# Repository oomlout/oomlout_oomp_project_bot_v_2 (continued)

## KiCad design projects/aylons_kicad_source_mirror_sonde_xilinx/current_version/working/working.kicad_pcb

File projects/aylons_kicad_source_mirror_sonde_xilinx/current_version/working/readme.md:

# kicad_source_mirror
 
## summary 
* id: aylons_kicad_source_mirror_sonde_xilinx
* user: aylons
* name: kicad_source_mirror
* board: sonde_xilinx
* repo: https://github.com/aylons/kicad-source-mirror
* src_file_repo_kicad_pcb: demos/sonde xilinx/sonde xilinx.kicad_pcb
* src_file_repo_kicad_pcb_link: https://github.com/aylons/kicad-source-mirror/tree/master/demos/sonde xilinx/sonde xilinx.kicad_pcb

* src_file_repo_sch: demos/sonde xilinx/sonde xilinx.sch
* src_file_repo_sch_link: https://github.com/aylons/kicad-source-mirror/tree/master/demos/sonde xilinx/sonde xilinx.sch
* full details link: https://github.com/oomlout/oomlout_oomp_project_bot_v_2/tree/main/projects/aylons_kicad_source_mirror_sonde_xilinx/current_version/working

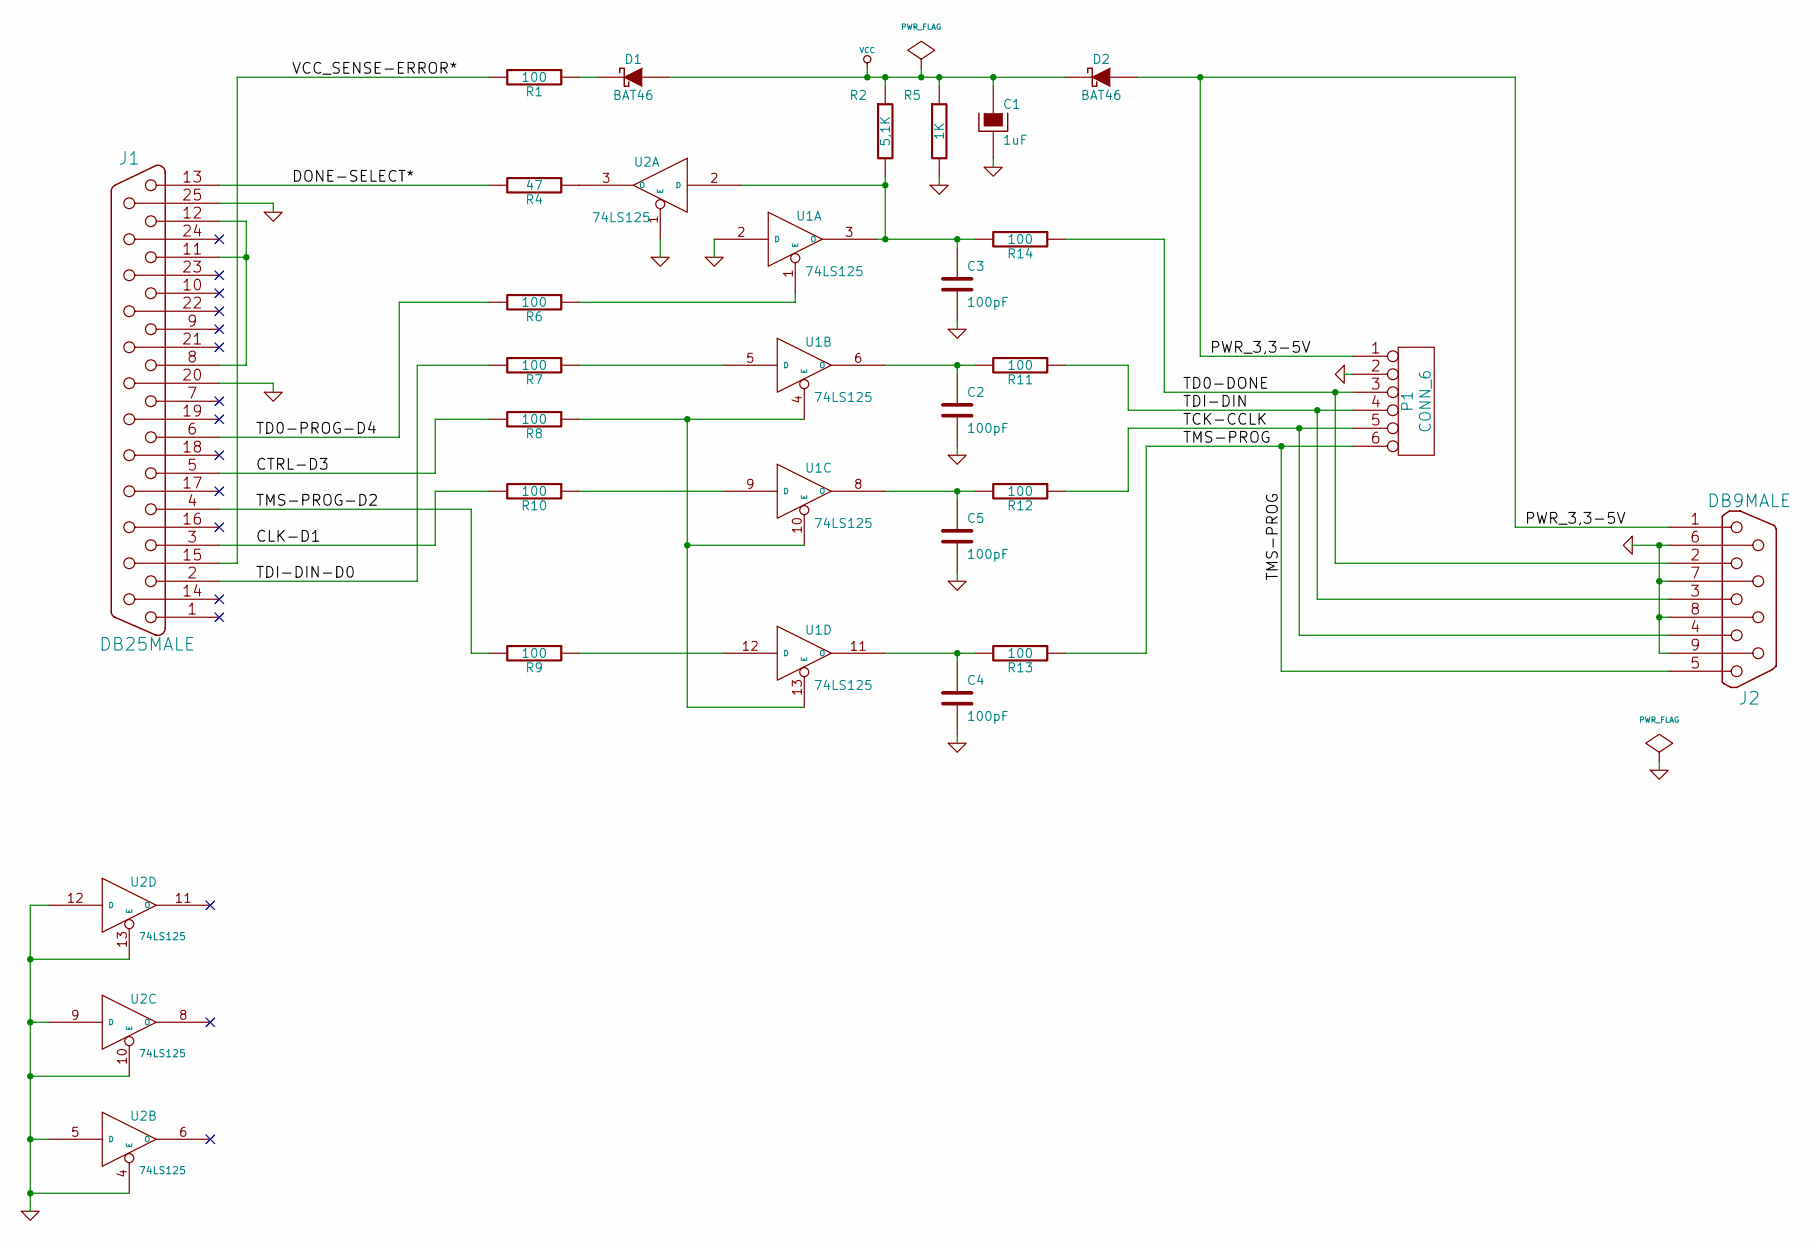
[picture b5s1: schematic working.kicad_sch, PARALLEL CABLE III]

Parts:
C1: 1uF; CP5
C2, C3, C4, C5: 100pF; C2
D1, D2: BAT46; D3
J1: DB25MALE; DB25M_CI
J2: DB9MALE; DB9M_CI_INVERT
P1: CONN_6; bornier6
R1, R6, R7, R8, R9, R10, R11, R12, R13, R14: 100; R4
R2: 5,1K; R4
R4: 47; R4
R5: 1K; R4
U1, U2: 74LS125; DIP-14__300_ELL

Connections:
/CLK-D1: J1.3, R10.2
/CTRL-D3: J1.5, R8.2
/DONE-SELECT*: J1.13, R4.2
/PWR_3,3-5V: D2.1 (A), J2.1, P1.1
/TCK-CCLK: J2.4, P1.5, R12.1
/TD0-DONE: J2.2, P1.3, R14.1
/TD0-PROG-D4: J1.6, R6.2
/TDI-DIN: J2.3, P1.4, R11.1
/TDI-DIN-D0: J1.2, R7.2
/TMS-PROG: J2.5, P1.6, R13.1
/TMS-PROG-D2: J1.4, R9.2
/VCC_SENSE-ERROR*: J1.15, R1.2
GND: C1.2, C2.2, C3.2, C4.2, C5.2, J1.20, J1.25, J2.6, J2.7, J2.8, J2.9, P1.2, R5.2, U1.2 (D), U1.7 (GND), U2.1 (E), U2.4 (E), U2.5 (D), U2.7 (GND), U2.9 (D), U2.10 (E), U2.12 (D), U2.13 (E)
unnamed: J1.8, J1.11, J1.12
unnamed: D1.2 (K), R1.1
unnamed: R4.1, U2.3 (O)
unnamed: R7.1, U1.5 (D)
unnamed: R10.1, U1.9 (D)
unnamed: R6.1, U1.1 (E)
unnamed: R9.1, U1.12 (D)
unnamed: R8.1, U1.4 (E), U1.10 (E), U1.13 (E)
unnamed: C4.1, R13.2, U1.11 (O)
unnamed: C2.1, R11.2, U1.6 (O)
unnamed: C5.1, R12.2, U1.8 (O)
unnamed: C3.1, R2.2, R14.2, U1.3 (O), U2.2 (D)
VCC: C1.1, D1.1 (A), D2.2 (K), R2.1, R5.1, U1.14 (VCC), U2.14 (VCC)

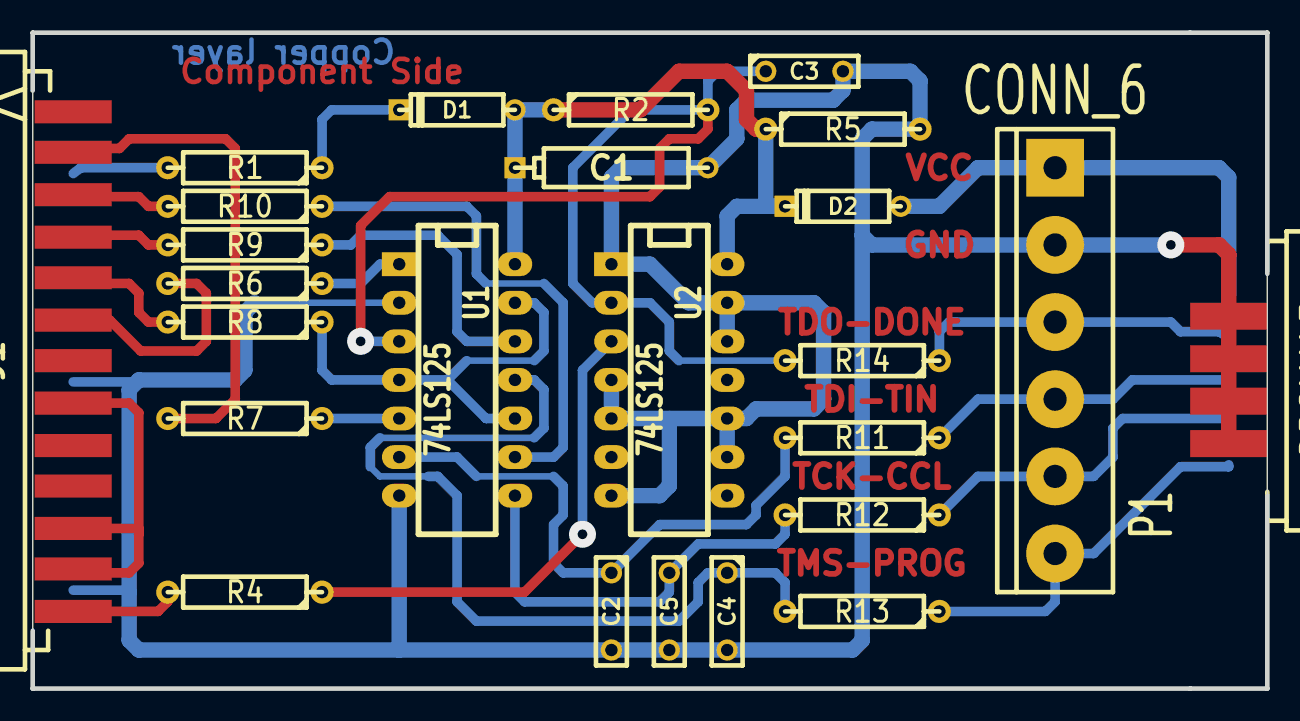
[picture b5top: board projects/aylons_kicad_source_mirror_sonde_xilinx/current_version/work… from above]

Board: 2 copper layers, 81.3 x 43.2 mm, 25 parts (0 on the bottom side), 26 nets.

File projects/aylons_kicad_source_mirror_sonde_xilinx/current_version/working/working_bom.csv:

"Id";"Designator";"Footprint";"Quantity";"Designation";"Supplier and ref";
1;"R8,R13,R14,R7,R1,R9,R12,R10,R6,R11";"R4";10;"100";;;
2;"R5";"R4";1;"1K";;;
3;"J1";"DB25M_CI";1;"DB25MALE";;;
4;"R2";"R4";1;"5,1K";;;
5;"C4,C5,C2,C3";"C2";4;"100pF";;;
6;"U1,U2";"14DIP-ELL300";2;"74LS125";;;
7;"D2,D1";"D3";2;"BAT46";;;
8;"J2";"DB9M_CI_INVERT";1;"DB9MALE";;;
9;"P1";"bornier6";1;"CONN_6";;;
10;"C1";"CP5";1;"1uF";;;
11;"R4";"R4";1;"47";;;
